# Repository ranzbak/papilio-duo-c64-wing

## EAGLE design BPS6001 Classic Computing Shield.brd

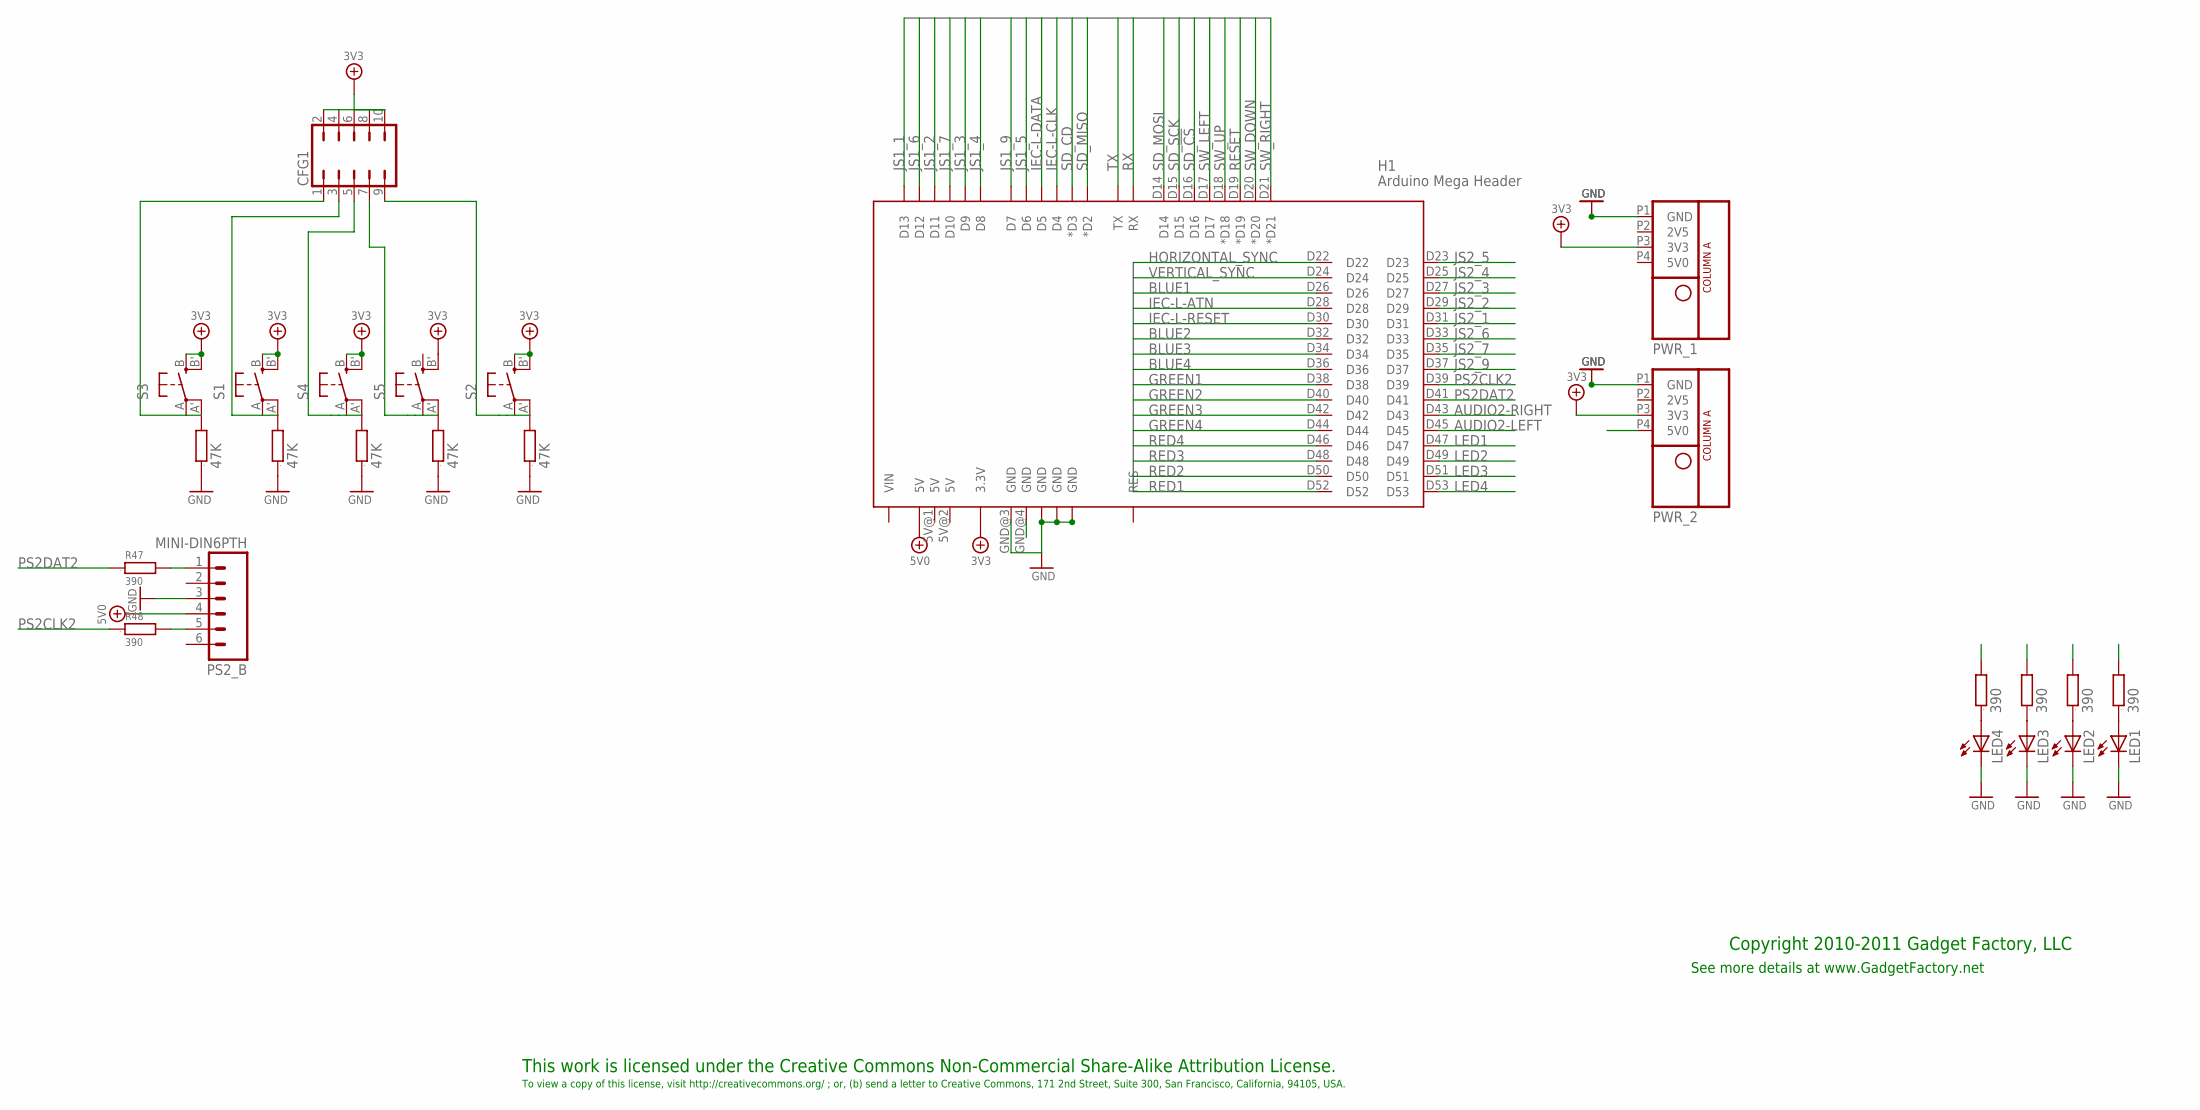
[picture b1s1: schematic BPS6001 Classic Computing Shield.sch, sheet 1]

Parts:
CFG1: JP5Q; PARTNO M20-9720545
H1: Arduino Mega Header; AMEGA_SHIELD_NOANALOG; PARTNO Arduino_Mega_Header
LED1, LED2, LED3, LED4: LEDCHIPLED_0603; CHIPLED_0603; PARTNO LTST-C190GKT
LOGO1: BUTTERFLY_LOGO
PS2_B: MINI-DIN6PTH; MINI-DIN6
PWR_1, PWR_2: POWER_ONLYNOTEXT; POWER_NO_TEXT
R9, R10, R11, R17, R18: 47K; 0603; PARTNO RMCF0603JT47K0
R26, R27, R43, R44, R47, R48: 390; 0603; PARTNO RMCF0603JT390R
S1, S2, S3, S4, S5: EVQQ2; EVQ-Q2; PARTNO PTS525SM10SMTR LFS

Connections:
3V3_PWR6: CFG1.2, CFG1.4, CFG1.6, CFG1.8, CFG1.10, H1.3.3V, S1.B (S), S1.B' (S1), S2.B (S), S2.B' (S1), S3.B (S), S3.B' (S1), S4.B (S), S4.B' (S1), S5.B' (S1); also elsewhere on the board
3V3_PWR7: PWR_2.P3 (3V3)
5V0: H1.5V@0 (5V); also elsewhere on the board
5V0_PS2: PS2_B.4, PWR_2.P4 (5V0)
AUDIO2-LEFT: H1.D45; also elsewhere on the board
AUDIO2-RIGHT: H1.D43; also elsewhere on the board
BLUE1: H1.D26; also elsewhere on the board
BLUE2: H1.D32; also elsewhere on the board
BLUE3: H1.D34; also elsewhere on the board
BLUE4: H1.D36; also elsewhere on the board
GND: H1.GND@0 (GND), H1.GND@1 (GND), H1.GND@2 (GND), H1.GND@3 (GND), R9.1, R10.1, R11.1, R17.1, R18.1; also elsewhere on the board
GREEN1: H1.D38; also elsewhere on the board
GREEN2: H1.D40; also elsewhere on the board
GREEN3: H1.D42; also elsewhere on the board
GREEN4: H1.D44; also elsewhere on the board
HORIZONTAL_SYNC: H1.D22; also elsewhere on the board
IEC-L-ATN: H1.D28; also elsewhere on the board
IEC-L-CLK: H1.D4; also elsewhere on the board
IEC-L-DATA: H1.D5; also elsewhere on the board
IEC-L-RESET: H1.D30; also elsewhere on the board
JOY_3V3: PWR_1.P3 (3V3); also elsewhere on the board
JOY_GND: H1.GND@4 (GND), LED1.C, LED2.C, LED3.C, LED4.C, PS2_B.3, PWR_1.P1 (GND), PWR_2.P1 (GND); also elsewhere on the board
JS1_1: H1.D13; also elsewhere on the board
JS1_2: H1.D11; also elsewhere on the board
JS1_3: H1.D9; also elsewhere on the board
JS1_4: H1.D8; also elsewhere on the board
JS1_5: H1.D6; also elsewhere on the board
JS1_6: H1.D12; also elsewhere on the board
JS1_7: H1.D10; also elsewhere on the board
JS1_9: H1.D7; also elsewhere on the board
JS2_1: H1.D31; also elsewhere on the board
JS2_2: H1.D29; also elsewhere on the board
JS2_3: H1.D27; also elsewhere on the board
JS2_4: H1.D25; also elsewhere on the board
JS2_5: H1.D23; also elsewhere on the board
JS2_6: H1.D33; also elsewhere on the board
JS2_7: H1.D35; also elsewhere on the board
JS2_9: H1.D37; also elsewhere on the board
LED1: H1.D47, R26.2
LED2: H1.D49, R27.2
LED3: H1.D51, R43.2
LED4: H1.D53, R44.2
unnamed: LED4.A, R44.1
unnamed: LED3.A, R43.1
unnamed: LED2.A, R27.1
unnamed: LED1.A, R26.1
unnamed: PS2_B.1, R47.2
unnamed: PS2_B.5, R48.2
PS2CLK2: H1.D39, R48.1
PS2DAT2: H1.D41, R47.1
RED1: H1.D52; also elsewhere on the board
RED2: H1.D50; also elsewhere on the board
RED3: H1.D48; also elsewhere on the board
RED4: H1.D46; also elsewhere on the board
RESET: CFG1.9, H1.D19 (*D19), R11.2, S2.A, S2.A' (P1)
RX: H1.RX
SD_!CS: H1.D16; also elsewhere on the board
SD_CD: H1.D3 (*D3); also elsewhere on the board
SD_MISO: H1.D2 (*D2); also elsewhere on the board
SD_MOSI: H1.D14; also elsewhere on the board
SD_SCK: H1.D15; also elsewhere on the board
SW_DOWN: CFG1.5, H1.D20 (*D20), R17.2, S4.A, S4.A' (P1)
SW_LEFT: CFG1.1, H1.D17, R9.2, S3.A, S3.A' (P1)
SW_RIGHT: CFG1.7, H1.D21 (*D21), R18.2, S5.A, S5.A' (P1)
SW_UP: CFG1.3, H1.D18 (*D18), R10.2, S1.A, S1.A' (P1)
TX: H1.TX
VERTICAL_SYNC: H1.D24; also elsewhere on the board

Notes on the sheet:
This work is licensed under the Creative Commons Non-Commercial Share-Alike Attribution License.
To view a copy of this license, visit http://creativecommons.org/ ; or, (b) send a letter to Creative Commons, 171 2nd Street, Suite 300, San Francisco, California, 94105, USA.
Copyright 2010-2011 Gadget Factory, LLC
See more details at www.GadgetFactory.net

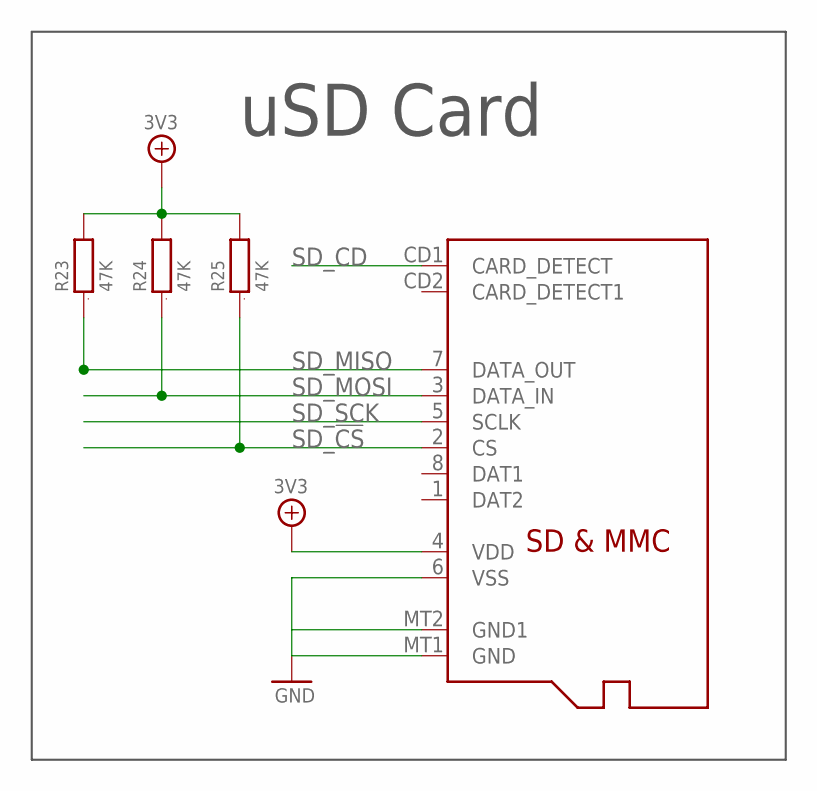
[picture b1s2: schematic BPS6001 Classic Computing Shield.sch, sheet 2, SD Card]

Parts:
R23, R24, R25: 47K; 0603; PARTNO RMCF0603JT47K0
SD1: MICROSD; PARTNO 101-00660-68-6

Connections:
3V3_PWR6: R23.2, R24.2, R25.2, SD1.4 (VDD); also elsewhere on the board
GND: SD1.6 (VSS), SD1.MT1 (GND), SD1.MT2 (GND1); also elsewhere on the board
SD_!CS: R25.1, SD1.2 (CS); also elsewhere on the board
SD_CD: SD1.CD1 (CARD_DETECT); also elsewhere on the board
SD_MISO: R23.1, SD1.7 (DATA_OUT); also elsewhere on the board
SD_MOSI: R24.1, SD1.3 (DATA_IN); also elsewhere on the board
SD_SCK: SD1.5 (SCLK); also elsewhere on the board

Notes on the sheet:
uSD Card

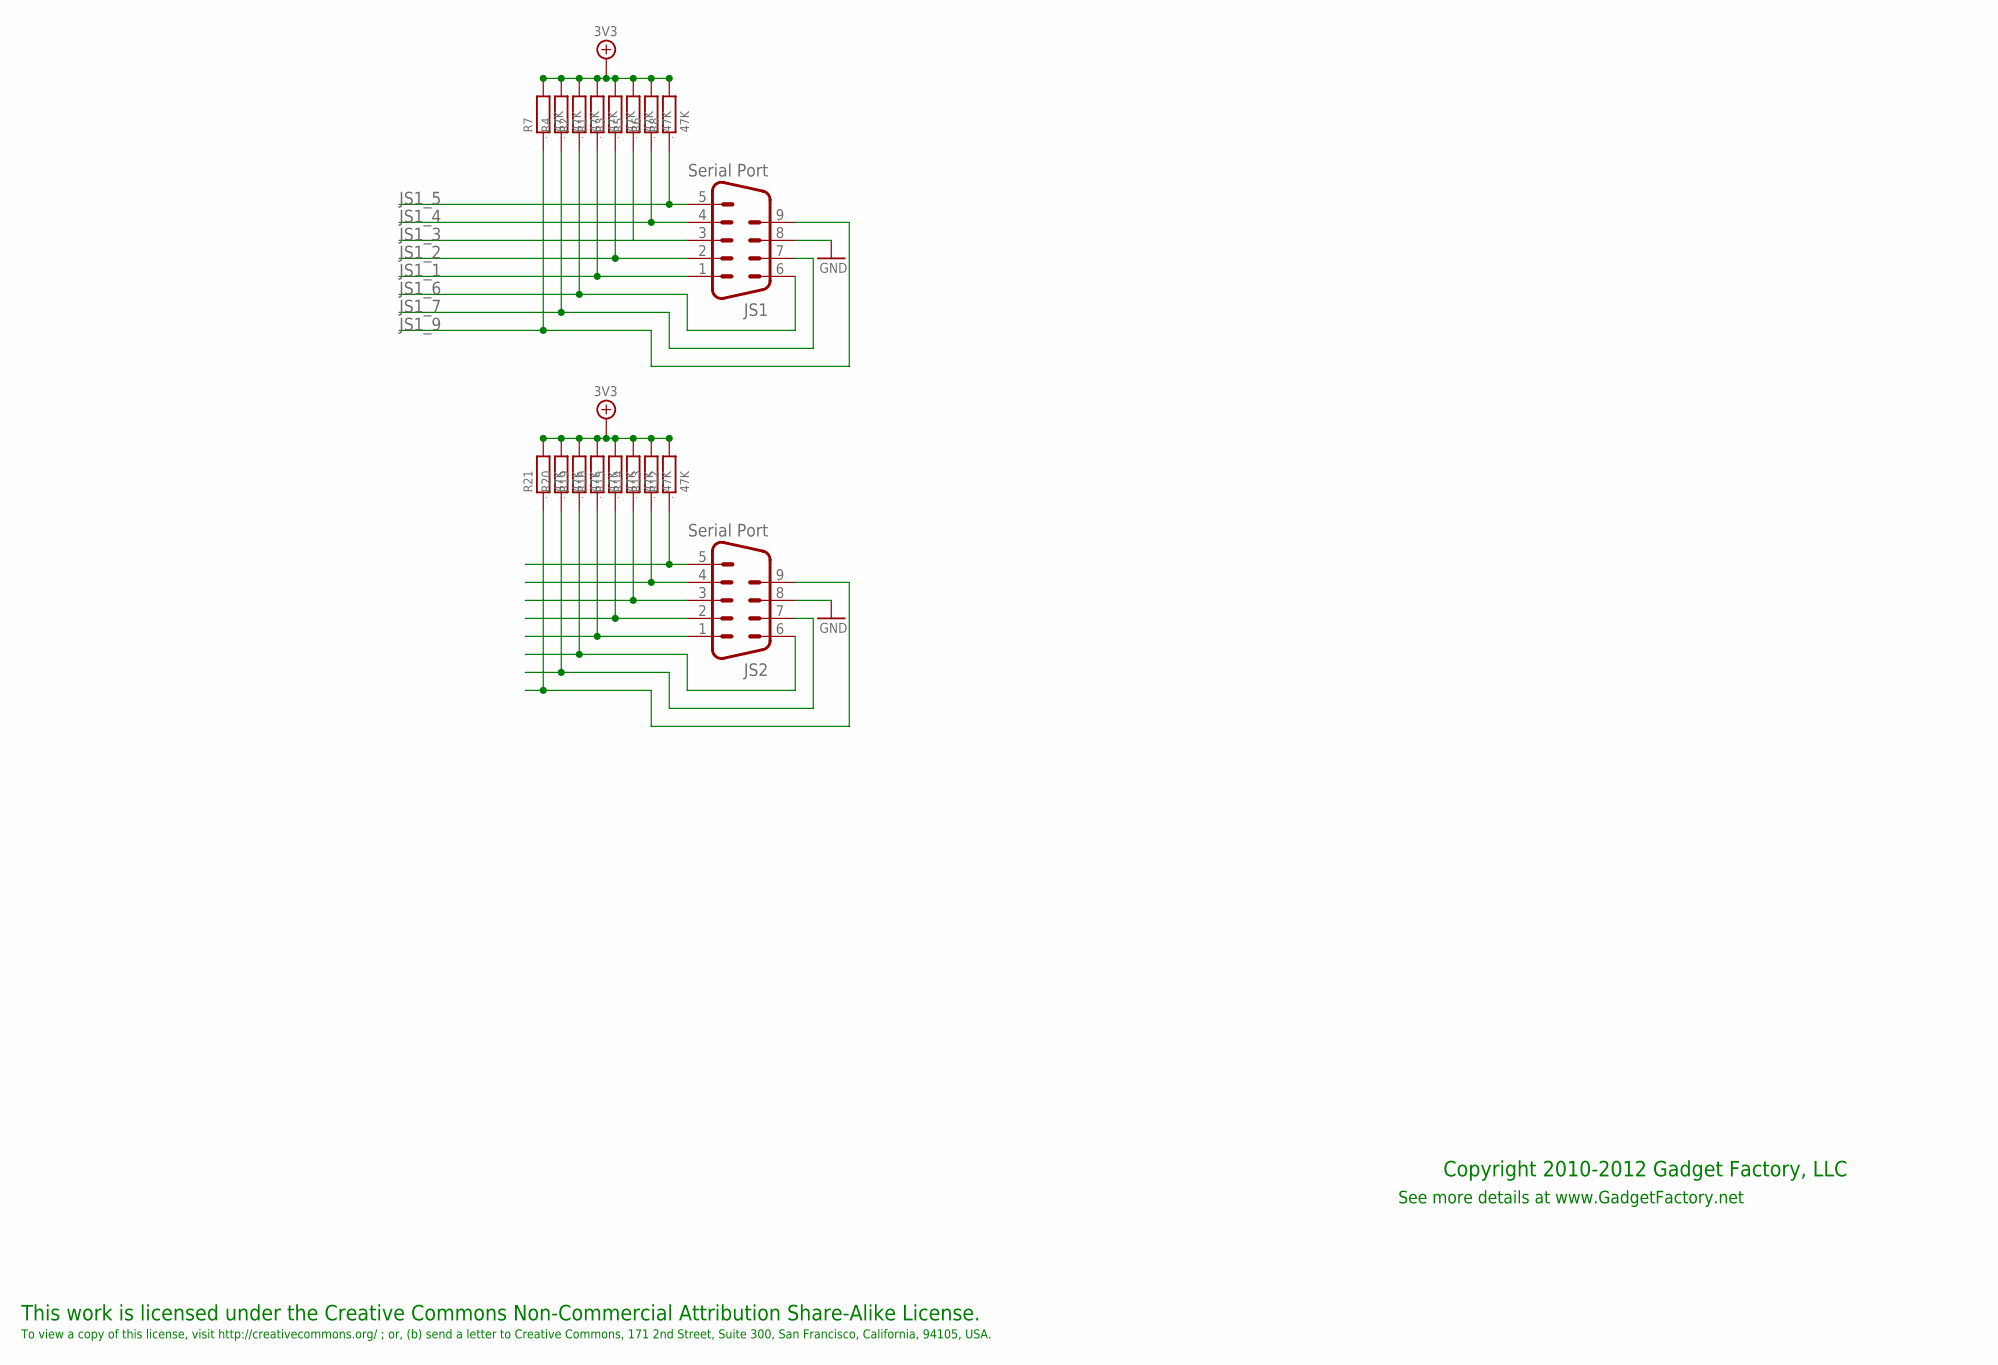
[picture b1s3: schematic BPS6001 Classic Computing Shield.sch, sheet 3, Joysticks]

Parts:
JS1, JS2: Serial Port; M09HP; PARTNO 10090097-P094VLF
R1, R2, R3, R4, R5, R6, R7, R8, R12, R13, R14, R15, R16, R19, R20, R21: 47K; 0603; PARTNO RMCF0603JT47K0

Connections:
3V3_PWR6: R1.2, R2.2, R3.2, R4.2, R5.2, R6.2, R7.2, R8.2; also elsewhere on the board
GND: JS1.8; also elsewhere on the board
JOY_3V3: R12.2, R13.2, R14.2, R15.2, R16.2, R19.2, R20.2, R21.2; also elsewhere on the board
JOY_GND: JS2.8; also elsewhere on the board
JS1_1: JS1.1, R1.1; also elsewhere on the board
JS1_2: JS1.2, R3.1; also elsewhere on the board
JS1_3: JS1.3, R5.1; also elsewhere on the board
JS1_4: JS1.4, R6.1; also elsewhere on the board
JS1_5: JS1.5, R8.1; also elsewhere on the board
JS1_6: JS1.6, R2.1; also elsewhere on the board
JS1_7: JS1.7, R4.1; also elsewhere on the board
JS1_9: JS1.9, R7.1; also elsewhere on the board
JS2_1: JS2.1, R16.1; also elsewhere on the board
JS2_2: JS2.2, R15.1; also elsewhere on the board
JS2_3: JS2.3, R14.1; also elsewhere on the board
JS2_4: JS2.4, R13.1; also elsewhere on the board
JS2_5: JS2.5, R12.1; also elsewhere on the board
JS2_6: JS2.6, R19.1; also elsewhere on the board
JS2_7: JS2.7, R20.1; also elsewhere on the board
JS2_9: JS2.9, R21.1; also elsewhere on the board

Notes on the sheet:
This work is licensed under the Creative Commons Non-Commercial Attribution Share-Alike License.
To view a copy of this license, visit http://creativecommons.org/ ; or, (b) send a letter to Creative Commons, 171 2nd Street, Suite 300, San Francisco, California, 94105, USA.
Copyright 2010-2012 Gadget Factory, LLC
See more details at www.GadgetFactory.net

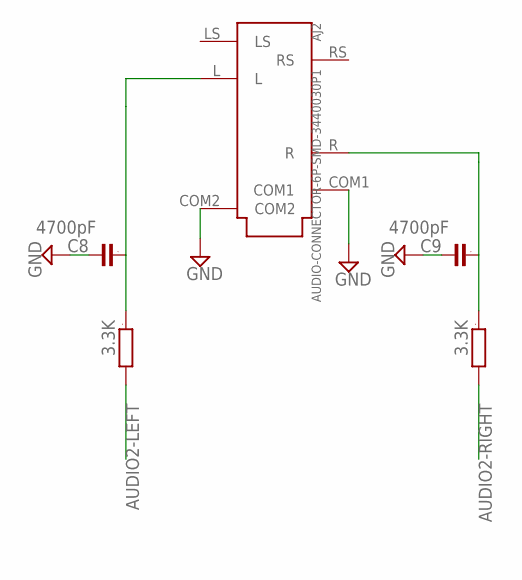
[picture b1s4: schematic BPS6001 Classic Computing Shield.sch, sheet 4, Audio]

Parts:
AJ2: AUDIO-CONNECTOR-6P-SMD-3440030P1; 6P-SMD-3.5; PARTNO 3440030P1
C8, C9: 4700pF; 0603; PARTNO C0603C472J5RACTU
R45, R46: 3.3K; 0603; PARTNO RMCF0603JT3K30

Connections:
AUDIO2-LEFT: R45.2; also elsewhere on the board
AUDIO2-RIGHT: R46.2; also elsewhere on the board
JOY_GND: AJ2.COM1, AJ2.COM2, C8.2, C9.2; also elsewhere on the board
unnamed: AJ2.L, C8.1, R45.1
unnamed: AJ2.R, C9.1, R46.1

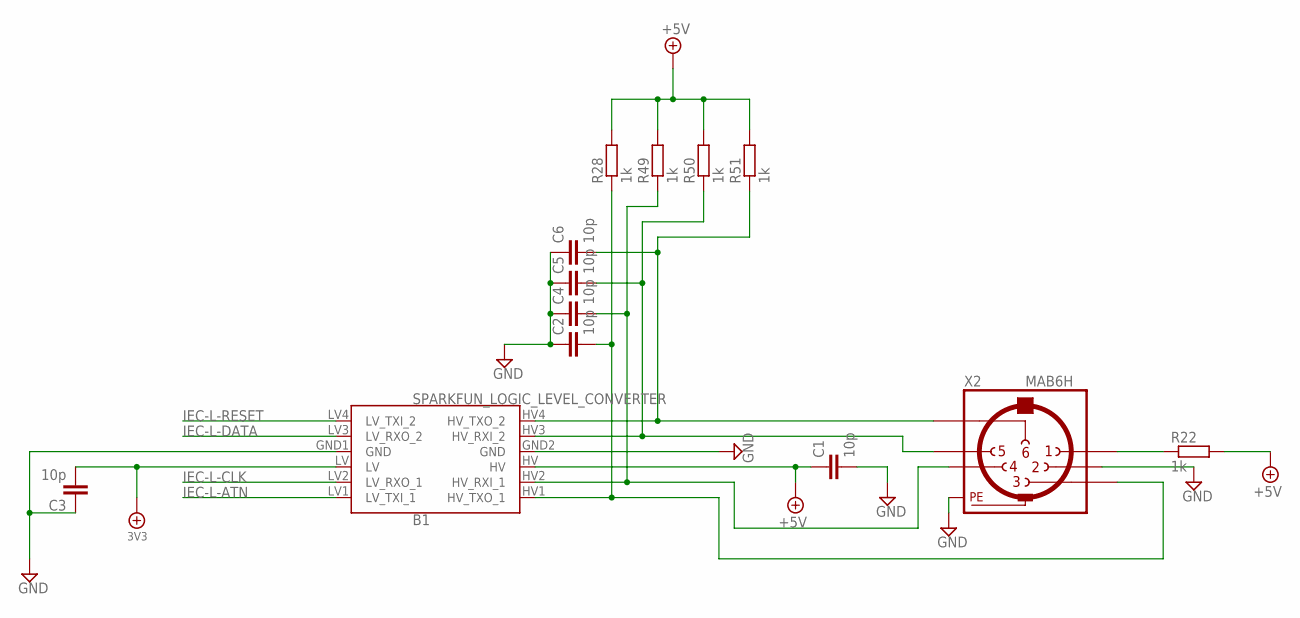
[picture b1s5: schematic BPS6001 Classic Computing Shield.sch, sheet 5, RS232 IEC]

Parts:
B1: SPARKFUN_LOGIC_LEVEL_CONVERTER
C1, C2, C3, C4, C5, C6: 10p; C0603
R22, R28, R49, R50, R51: 1k; R0603
X2: MAB6H

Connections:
3V3_PWR6: B1.LV, C3.2; also elsewhere on the board
5V0: B1.HV, C1.1, R22.2, R28.2, R49.2, R50.2, R51.2; also elsewhere on the board
GND: B1.GND1 (GND), B1.GND2 (GND), C1.2, C2.1, C3.1, C4.1, C5.1, C6.1, X2.2, X2.PE, X2.PE@ (PE); also elsewhere on the board
IEC-H-ATN: B1.HV1 (HV_TXO_1), C2.2, R28.1, X2.3
IEC-H-CLK: B1.HV2 (HV_RXI_1), C4.2, R49.1, X2.4
IEC-H-DATA: B1.HV3 (HV_RXI_2), C5.2, R50.1, X2.5
IEC-H-RESET: B1.HV4 (HV_TXO_2), C6.2, R51.1, X2.6
IEC-H-SRQ: R22.1, X2.1
IEC-L-ATN: B1.LV1 (LV_TXI_1); also elsewhere on the board
IEC-L-CLK: B1.LV2 (LV_RXO_1); also elsewhere on the board
IEC-L-DATA: B1.LV3 (LV_RXO_2); also elsewhere on the board
IEC-L-RESET: B1.LV4 (LV_TXI_2); also elsewhere on the board

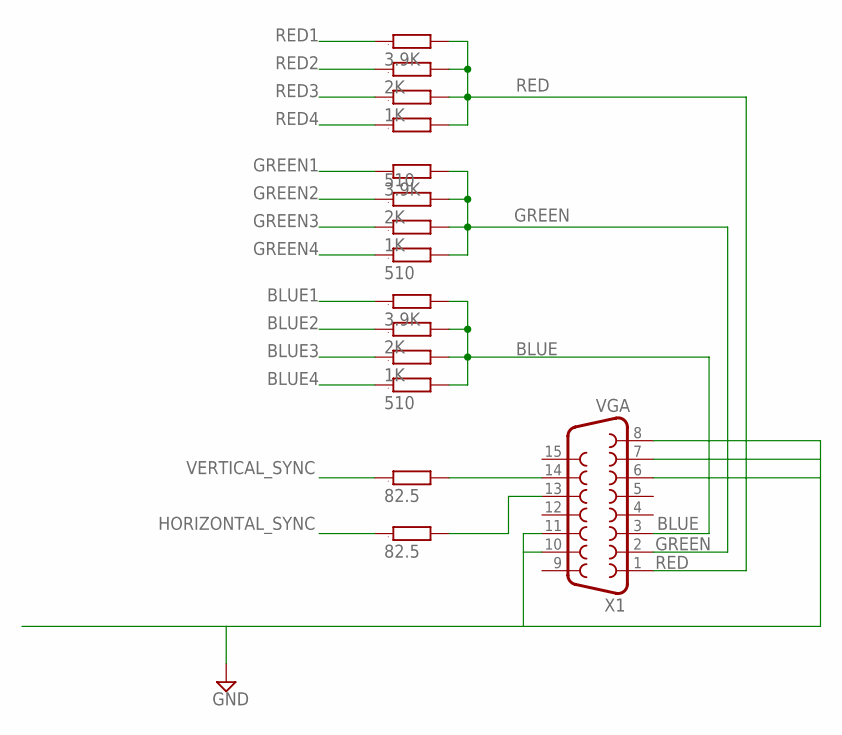
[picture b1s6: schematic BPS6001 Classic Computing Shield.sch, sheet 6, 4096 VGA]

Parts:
R29, R30: 82.5; 0603; PARTNO RMCF0603FT82R5
R31, R35, R42: 3.9K; 0603; PARTNO RMCF0603JT3K90
R32, R36, R41: 2K; 0603; PARTNO RMCF0603JT2K00
R33, R37, R40: 1K; 0603; PARTNO RMCF0603JT1K00
R34, R38, R39: 510; 0603; PARTNO RMCF0603JT510R
X1: VGA; HDF15H; PARTNO 1-1734530-1

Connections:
BLUE: R31.2, R32.2, R33.2, R34.2, X1.3
BLUE1: R31.1; also elsewhere on the board
BLUE2: R32.1; also elsewhere on the board
BLUE3: R33.1; also elsewhere on the board
BLUE4: R34.1; also elsewhere on the board
GND: X1.6, X1.7, X1.8, X1.10, X1.11; also elsewhere on the board
GREEN: R35.2, R36.2, R37.2, R38.2, X1.2
GREEN1: R35.1; also elsewhere on the board
GREEN2: R36.1; also elsewhere on the board
GREEN3: R37.1; also elsewhere on the board
GREEN4: R38.1; also elsewhere on the board
HORIZONTAL_SYNC: R29.1; also elsewhere on the board
unnamed: R29.2, X1.13
unnamed: R30.2, X1.14
RED: R39.2, R40.2, R41.2, R42.2, X1.1
RED1: R42.1; also elsewhere on the board
RED2: R41.1; also elsewhere on the board
RED3: R40.1; also elsewhere on the board
RED4: R39.1; also elsewhere on the board
VERTICAL_SYNC: R30.1; also elsewhere on the board

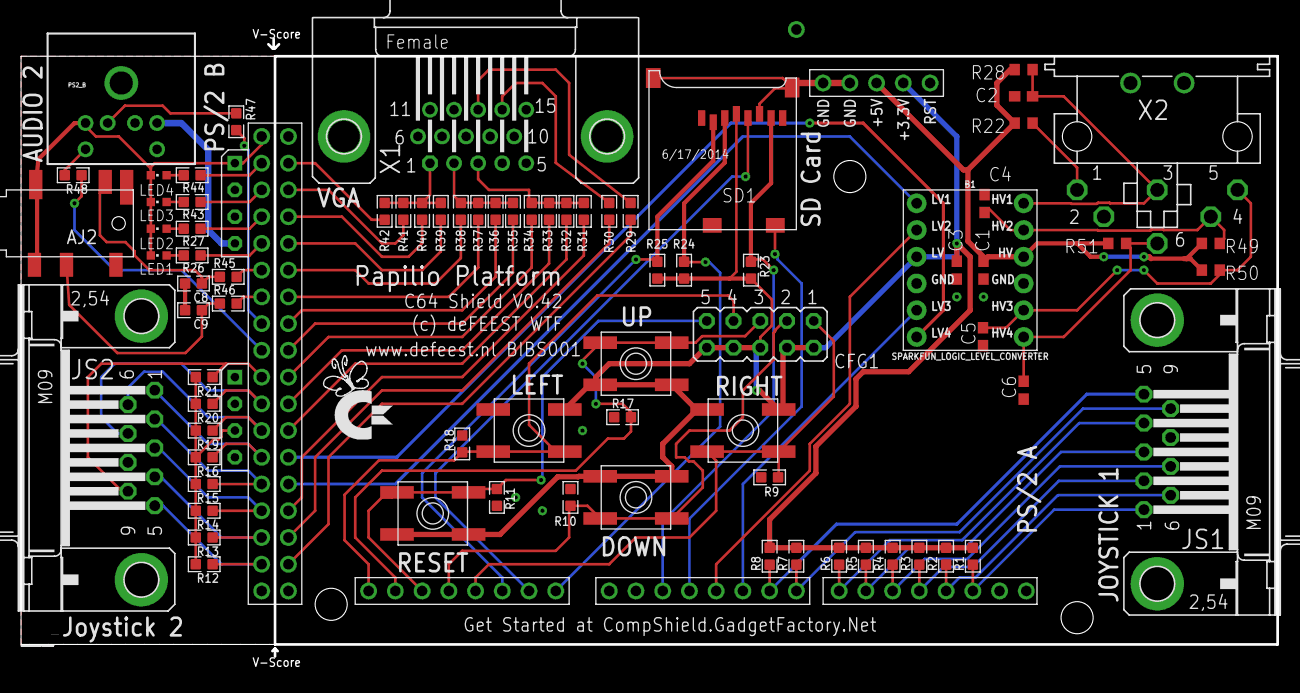
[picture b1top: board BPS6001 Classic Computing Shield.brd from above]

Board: 2 copper layers, 119.3 x 61.1 mm, 84 parts (0 on the bottom side), 76 nets.

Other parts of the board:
U$1, U$2, U$3: STAND-OFF-TIGHT

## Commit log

2019-06-02 Removed the other wings in the original project.
2019-06-20 First outline of design moved to Eagle 9.
2019-06-20 Fixed some issues, board is now without problems.
2019-07-06 Added BOM file to the project.

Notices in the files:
parts and their libraries:
SparkFun-Connectors: Licensing: CC v3.0 Share-Alike You are welcome to use this library for commercial purposes.
SparkFun-Boards: Licensing: Creative Commons ShareAlike 4.0 International - https://creativecommons.org/licenses/by-sa/4.0
